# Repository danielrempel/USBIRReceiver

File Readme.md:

USBIRReceiver — an Atmega8L-based USB device to receive IR NEC commands from remote
control and configurable host software to run commands upon receiving
configured codes.

Device firmware is using Objective Development's V-USB (https://www.obdev.at/vusb/).
Host software uses Ben Hoyt's 'inih' library (https://github.com/benhoyt/inih).

Host software launches commands from its configuration file so it is
important to run the program from ordinary user. The user will need
rights to access the usb device.
I expect that adding a udev rule like this one:
> SUBSYSTEM=="usb", ATTR{idVendor}=="16c0", ATTR{idProduct}=="05dc", GROUP==<group>, MODE="0666"
will be enough.

Building:
* put usbdrv folder from OBdev's V-USB to the firmware folder without
	replacing the usbconfig.h file
* put Ben Hoyt's 'inih' library souces (ini.c,ini.h) to <project-root>/inih/
* firmware: cd firmware; make; make flash [; make fuse -- in case you need to re-fuse]
* host-side: cd host-side; make

NOTE: firmware's Makefile is configured to work with avrdude & USBAsp

NOTE: commands in ini file must not contain quoted spaces, up to 20 args

NOTE: repeat cmd from IR NEC is sent as 0xFA/0xFA by the receiver
		according to the standard it may be sent 104ms after the initial press
		from my experience it's not enough, so I just did code any reaction to it
		(on my remote a single click is constantly treated as a click + repeat)

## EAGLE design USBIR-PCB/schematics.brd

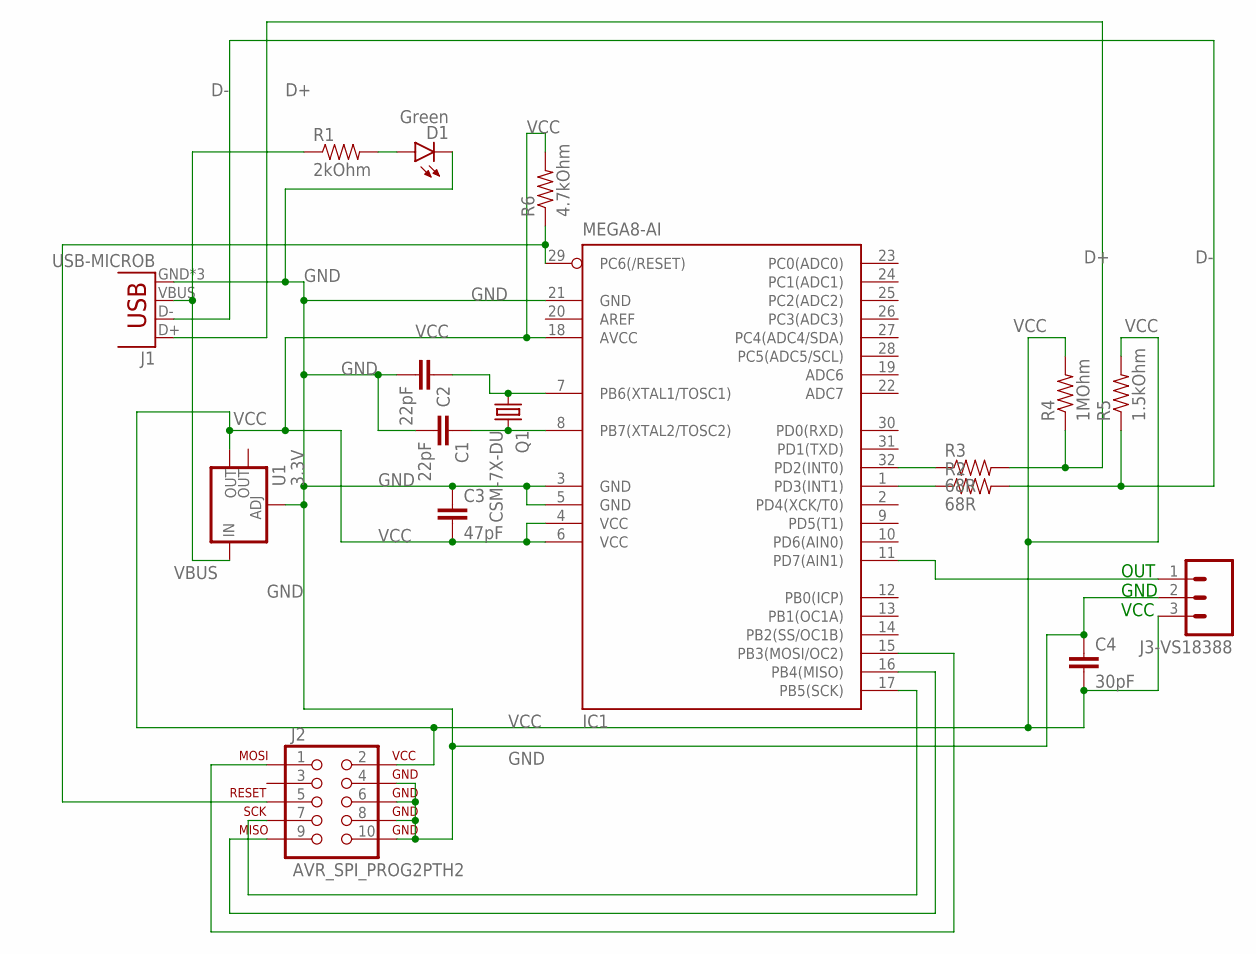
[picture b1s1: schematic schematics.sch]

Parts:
C1, C2: 22pF; 1206
C3: 47pF; 1206
C4: 30pF; 1206
D1: Green; LED-1206
IC1: MEGA8-AI; TQFP32-08
J1: USB-MICROB
J2: AVR_SPI_PROG2PTH2; 2X5-SHROUDED
J3-VS18388: M03PTH; 1X03
Q1: CSM-7X-DU
R1: 2kOhm; 1206
R2, R3: 68R; 1206
R4: 1MOhm; 1206
R5: 1.5kOhm; 1206
R6: 4.7kOhm; 1206
U1: 3.3V; SOT223

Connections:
D+: J1.D+, R3.2, R4.1
D-: J1.D-, R2.2, R5.1
GND: C1.2, C2.2, C3.1, C4.1, D1.C, IC1.3 (GND), IC1.5 (GND), IC1.21 (GND), J1.GND, J1.MT1 (GND), J1.MT2 (GND), J2.4 (GND), J2.6 (GND), J2.8 (GND), J2.10 (GND), J3-VS18388.2, U1.1 (ADJ)
unnamed: C1.1, IC1.8 (PB7(XTAL2/TOSC2)), Q1.2
unnamed: D1.A, R1.2
unnamed: C2.1, IC1.7 (PB6(XTAL1/TOSC1)), Q1.1
unnamed: IC1.11 (PD7(AIN1)), J3-VS18388.1
unnamed: IC1.16 (PB4(MISO)), J2.9 (MISO)
unnamed: IC1.17 (PB5(SCK)), J2.7 (SCK)
unnamed: IC1.15 (PB3(MOSI/OC2)), J2.1 (MOSI)
unnamed: IC1.29 (PC6(/RESET)), J2.5 (RESET), R6.1
unnamed: IC1.32 (PD2(INT0)), R3.1
unnamed: IC1.1 (PD3(INT1)), R2.1
VBUS: J1.VBUS, R1.1, U1.3 (IN)
VCC: C3.2, C4.2, IC1.4 (VCC), IC1.6 (VCC), IC1.18 (AVCC), J2.2 (VCC), J3-VS18388.3, R4.2, R5.2, R6.2, U1.2 (OUT)

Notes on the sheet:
OUT GND VCC

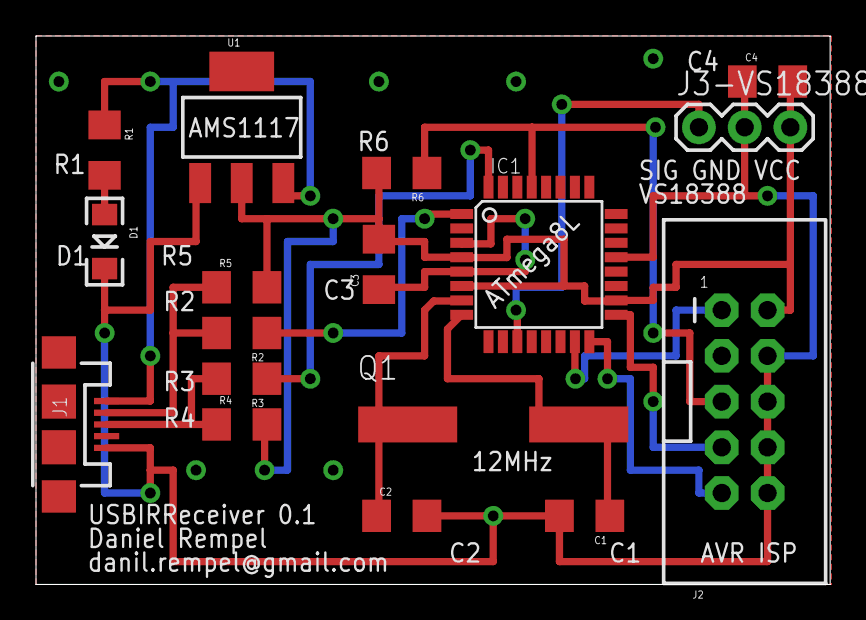
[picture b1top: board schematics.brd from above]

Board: 2 copper layers, 44.1 x 30.5 mm, 17 parts (0 on the bottom side), 15 nets.

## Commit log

2016-09-28 Initial: everyting's ready
2016-09-28 Change Readme.md a bit
2016-09-28 Update Readme.md
    Fix newlines
2017-03-08 control.c: restyle code
2017-03-08 config.ini: better pactl cmds etc
2017-03-08 USBIR-PCB: add PCB and Gerber files for the v0.1 PCB

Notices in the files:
parts and their libraries:
SparkFun-Retired: Licensing:Creative Commons ShareAlike 4.0 International - https://creativecommons.org/licenses/by-sa/4.0
